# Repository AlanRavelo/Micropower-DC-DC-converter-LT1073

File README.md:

# LT1073_LinearTechnology

El LT1073 es un circuito integrado de Linear Technology (ahora parte de Analog Devices) que se utiliza como convertidor de corriente continua (DC-DC). Es un convertidor de tipo step-up (boost) que convierte una entrada de voltaje de CC de bajo nivel a una salida de voltaje de CC de nivel más alto.

El LT1073 puede funcionar con una entrada de voltaje de CC de 2,7 V a 10 V y generar una salida de voltaje de CC de hasta 60 V. Tiene una corriente de salida máxima de 1,5 A y un rendimiento de hasta el 94% en algunas aplicaciones.

El circuito integrado LT1073 es capaz de operar con un rango de frecuencia ajustable, lo que permite optimizar su rendimiento para aplicaciones específicas. Además, cuenta con una serie de características de protección, como protección contra cortocircuitos, sobrecalentamiento y sobretensión.

El LT1073 es ampliamente utilizado en aplicaciones que requieren una fuente de alimentación de nivel superior a partir de una fuente de alimentación de nivel inferior, como en sistemas de iluminación LED, sistemas de control de motores, cargadores de baterías, entre otros. El circuito integrado es muy popular debido a su bajo costo, alta eficiencia y flexibilidad en cuanto a su configuración y aplicaciones.

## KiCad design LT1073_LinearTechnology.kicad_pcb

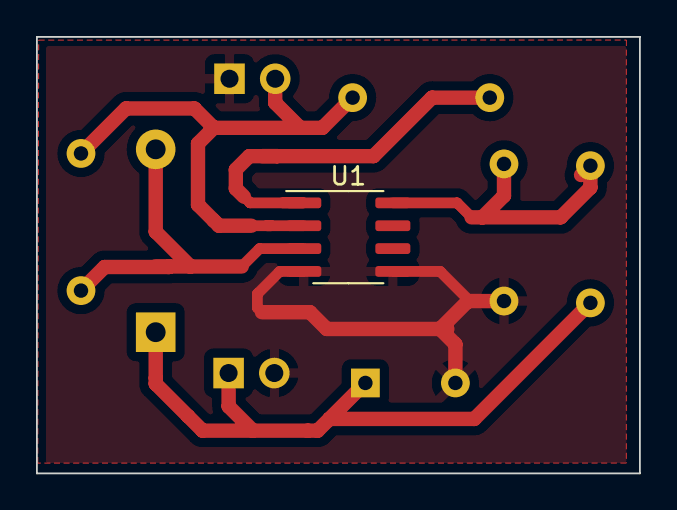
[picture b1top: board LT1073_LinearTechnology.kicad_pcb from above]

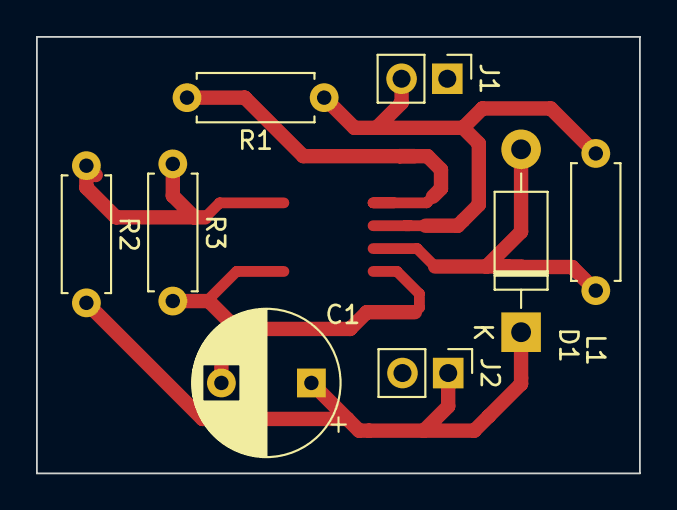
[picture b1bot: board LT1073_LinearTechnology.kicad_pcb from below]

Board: 2 copper layers, 33.5 x 24.2 mm, 9 parts (8 on the bottom side), 6 nets.

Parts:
C1: 100u; CP_Radial_D8.0mm_P5.00mm
D1: 1N5818; D_DO-41_SOD81_P10.16mm_Horizontal
J1, J2: Conn_01x02; PinHeader_1x02_P2.54mm_Vertical
L1: 120u; R_Axial_DIN0207_L6.3mm_D2.5mm_P7.62mm_Horizontal
R1: 220; R_Axial_DIN0207_L6.3mm_D2.5mm_P7.62mm_Horizontal
R2: 536k; R_Axial_DIN0207_L6.3mm_D2.5mm_P7.62mm_Horizontal
R3: 40.2k; R_Axial_DIN0207_L6.3mm_D2.5mm_P7.62mm_Horizontal
U1: LT1073CS-5; SOIC-8_3.9x4.9mm_P1.27mm

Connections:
GND: C1.2, J1.1, J2.2, R3.2, U1.4 (SW2), U1.5 (GND)
unnamed: C1.1, D1.1 (K), J2.1, R2.2
unnamed: D1.2 (A), L1.2, U1.3 (SW1)
unnamed: J1.2, L1.1, R1.1, U1.2 (Vin)
unnamed: R1.2, U1.1 (Ilim)
unnamed: R2.1, R3.1, U1.8 (SENSE)
